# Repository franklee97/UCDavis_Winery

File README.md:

# UCDavis_Winery

This repo contains all the information regarding my project at UC Davis RMI Winery. The goal of the project was to come up with a system that can collect and record data from a fermentation tank inside the winery. The data that were collected were Brix, or sugar concentration of a wine, Redox, and temperature. This system consisted of a PCB carrier board with mounting holes and necessary electrical connections, modules that either plugged into the mounting holes of the carrier board or resided on a din rail, and a box to hold all the components and wires. This repo has software information as well as hardware and layout information of the box. The system was only tested with one fermentation tank, but it is capable of expanding the number of tanks by a simple change in code. It also has the capability of sending data wirelessly via Bluetooth or XBee.

## BOM
This folder has the Bill of Materials(BOM) necessary for this project. The parts were ordered in four different batches. `Final.xlsx` contains all the components that are necessary for this project as some parts were never used from other orders.

## Code
This folder contains the code necessary to collect data. It contains two Arduino code, `data_collection_brix.ino` and `data_collection_redox.ino`. They both use `ModbusMaster.h` library to read values from the slave devices and store into SD cards, but the brix code reads two sensors' data while the redox code read one sensor's data. The polling rates for each code are also different. The code was written for Arduino Mega board, but any Arduino boards with at least two Serial ports will suffice. 

### Data Format
The data are stored as `.csv` file. The sample data for each code are inside each code folder. The name of the file uses the following format: `DATA[month][date].csv`. For example, if it is a data file from January 5th, the filename would be `DATA15.csv`. A new file was created every day to prevent an overload inside one file. More information about how this was done is in the comments for each code.

## Diagram
This folder contains two files, `Circuit_Diagram.png` and `Data_Flow_2.0.pdf`. `Circuit_Diagram.png` shows a circuit level diagram of how everything is being powered. It also shows data communication as well. `Data_Flow_2.0.pdf` is a diagram that specifically shows how data is being transferred between the modules inside the system. `Circuit_Diagram.png` was created using EAGLE and `Data_Flow_2.0.pdf` was created using Microsoft Vizio.

## Schematic
This folder contains a folder named `carrier_final` which has the necessary EAGLE files for the carrier PCB. It also has a top and bottom layout pictures given by Oshpark. The folder contains `Archives` folder that has previous EAGLE designs.

## Solidworks
This folder has `.SLDPRT` files that was necessary for the design of the box. Some components were downloaded from the manufacturing websites, and some were created by me. `Final.SLDPRT` has all the components.

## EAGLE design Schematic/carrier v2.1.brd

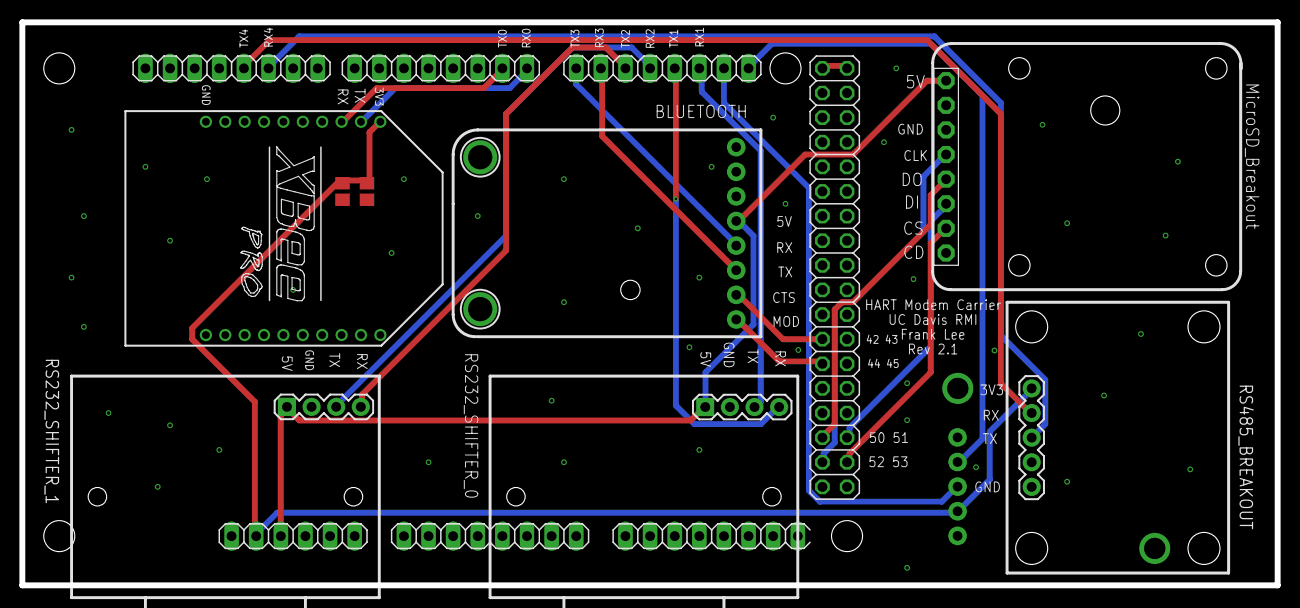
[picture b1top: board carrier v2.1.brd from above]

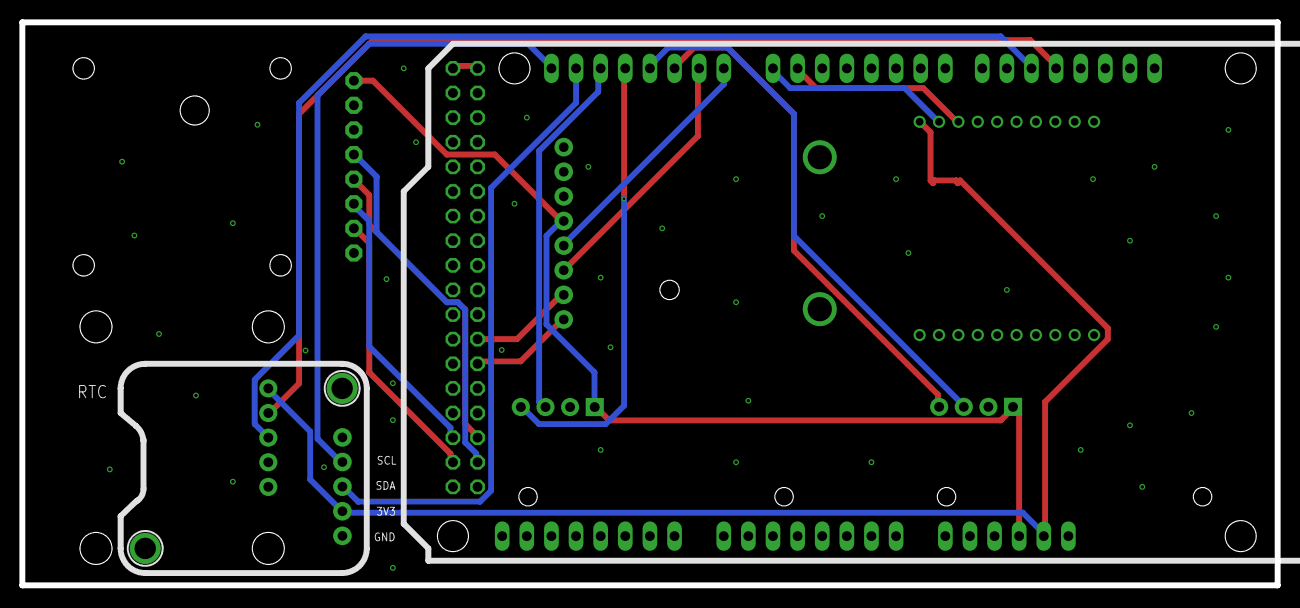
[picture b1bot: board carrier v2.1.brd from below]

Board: 2 copper layers, 129.5 x 58.1 mm, 18 parts (4 on the bottom side), 22 nets.

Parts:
BLUETOOTH: 1X08_ROUND_76
C18: 1uF; C0805
C19: 8.3pF; C0805
IC1: MEGA_ARDUINO
JP6, JP7, JP8, JP15: STAND-OFF
MICROSD_BREAKOUT: 1X08-BIG
RS232_SHIFTER_0, RS232_SHIFTER_1: 1X04
RS485_BREAKOUT: 1X05
RTC: 1X05_ROUND_76
U$1, U$4: MOUNTINGHOLE2.0; MOUNTINGHOLE_2.0_PLATED
U$28, U$29: MOUNTINGHOLE2.5; MOUNTINGHOLE_2.5_PLATED
XB1: XBEE-PRO

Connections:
232_RX_0: IC1.26, RS232_SHIFTER_0.4
232_RX_1: IC1.28, RS232_SHIFTER_1.4
232_TX_0: IC1.25, RS232_SHIFTER_0.3
232_TX_1: IC1.27, RS232_SHIFTER_1.3
+5V: IC1.47, IC1.48
ARDUINO_3V3: C18.1, C19.1, IC1.2, RS485_BREAKOUT.1, RTC.2, XB1.1
ARDUINO_5V: BLUETOOTH.4, IC1.3, MICROSD_BREAKOUT.1, RS232_SHIFTER_0.1, RS232_SHIFTER_1.1
BLUETOOTH_CTS: BLUETOOTH.7, IC1.69
BLUETOOTH_MOD: BLUETOOTH.8, IC1.71
BLUETOOTH_RX: BLUETOOTH.5, IC1.30
BLUETOOTH_TX: BLUETOOTH.6, IC1.29
CLK: IC1.79, MICROSD_BREAKOUT.4
CS: IC1.80, MICROSD_BREAKOUT.7
DI: IC1.78, MICROSD_BREAKOUT.6
DO: IC1.77, MICROSD_BREAKOUT.5
GND: BLUETOOTH.2, C18.2, C19.2, IC1.4, IC1.5, IC1.45, IC1.81, IC1.82, MICROSD_BREAKOUT.3, RS232_SHIFTER_0.2, RS232_SHIFTER_1.2, RS485_BREAKOUT.5, RTC.1, XB1.10
RS485_RX: IC1.42, RS485_BREAKOUT.2
RS485_TX: IC1.41, RS485_BREAKOUT.3
SCL: IC1.23, RTC.4
SDA: IC1.24, RTC.3
XBEE_RX: IC1.32, XB1.3
XBEE_TX: IC1.31, XB1.2

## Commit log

2019-04-24 Added codes
2019-04-24 Added schematics
2019-04-24 added solidworks, circuit diagram, and archived carrier designs
2019-04-24 layer view of the final board
2019-04-24 Update circuit diagram
2019-04-24 Update data flow and circuit diagram
2019-04-24 Clean
2019-04-24 Update BOM
2019-04-24 Added sample data
2019-04-24 Added RS485 modules in BOM
2019-04-24 Added commends

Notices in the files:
parts and their libraries:
SparkFun-Connectors: Licensing: Creative Commons ShareAlike 4.0 International - https://creativecommons.org/licenses/by-sa/4.0
microbuilder: This work is placed in the public domain, and may be freely used for commercial and non-commercial work with the following conditions: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
